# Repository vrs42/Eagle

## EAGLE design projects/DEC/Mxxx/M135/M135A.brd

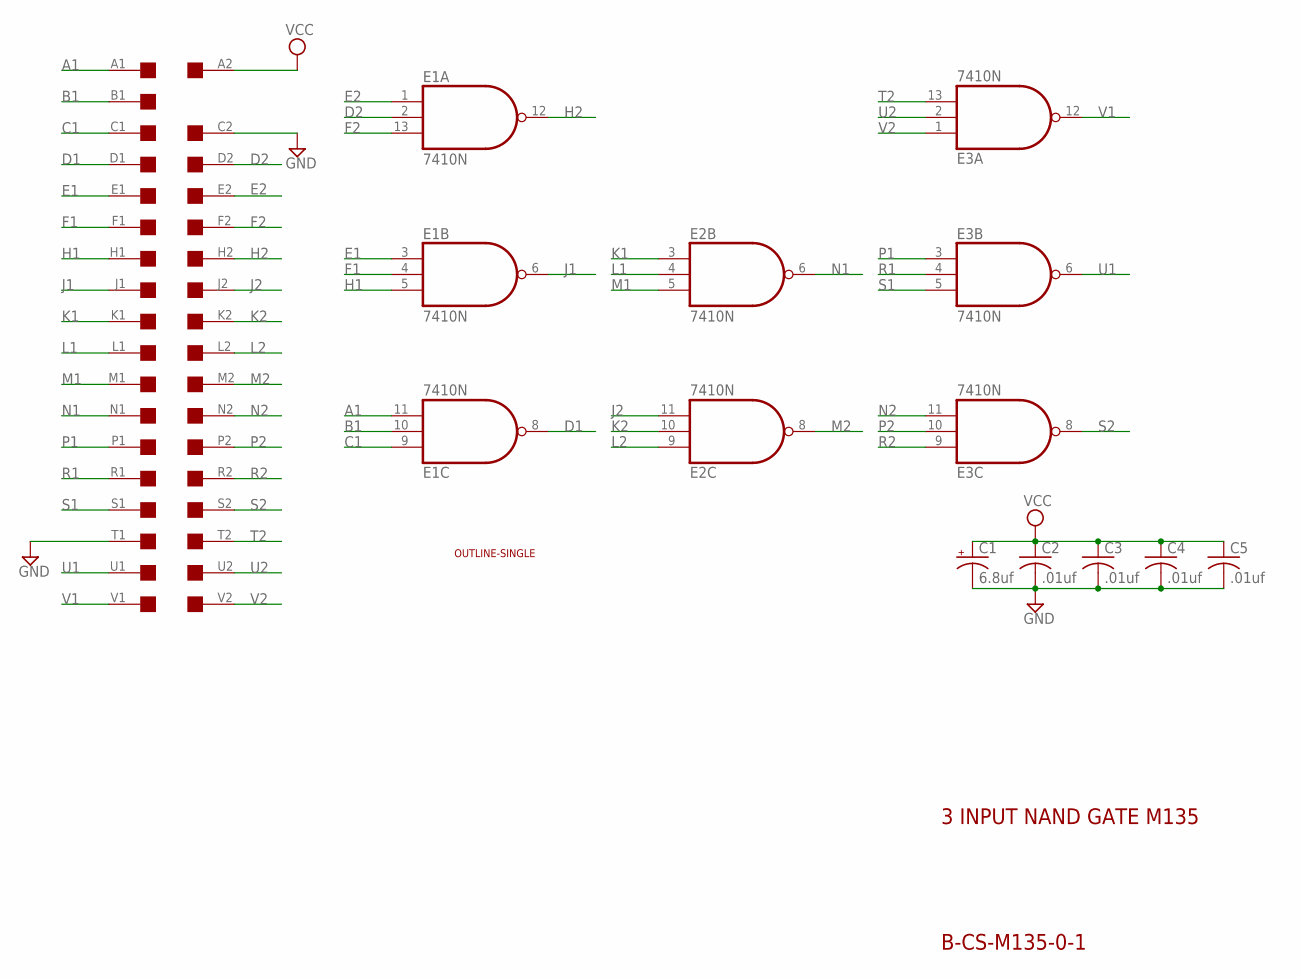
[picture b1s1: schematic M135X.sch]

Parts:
C1: 6.8uf; E15-5
C2, C3, C4, C5: .01uf; C050-025X075
E1, E2, E3: 7410N; DIL14
U$1: SINGLE; EDGE-CON2
U$4: OUTLINE-SINGLE; SINGLE

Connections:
A1: E1.11 (I2), U$1.A1
B1: E1.10 (I1), U$1.B1
C1: E1.9 (I0), U$1.C1
D1: E1.8 (O), U$1.D1
D2: E1.2 (I1), U$1.D2
E1: E1.3 (I0), U$1.E1
E2: E1.1 (I0), U$1.E2
F1: E1.4 (I1), U$1.F1
F2: E1.13 (I2), U$1.F2
GND: C1.-, C2.2, C3.2, C4.2, C5.2, E1.7 (GND), E2.7 (GND), E3.7 (GND), U$1.C2, U$1.T1
H1: E1.5 (I2), U$1.H1
H2: E1.12 (O), U$1.H2
J1: E1.6 (O), U$1.J1
J2: E2.11 (I2), U$1.J2
K1: E2.3 (I0), U$1.K1
K2: E2.10 (I1), U$1.K2
L1: E2.4 (I1), U$1.L1
L2: E2.9 (I0), U$1.L2
M1: E2.5 (I2), U$1.M1
M2: E2.8 (O), U$1.M2
N1: E2.6 (O), U$1.N1
N2: E3.11 (I2), U$1.N2
P1: E3.3 (I0), U$1.P1
P2: E3.10 (I1), U$1.P2
R1: E3.4 (I1), U$1.R1
R2: E3.9 (I0), U$1.R2
S1: E3.5 (I2), U$1.S1
S2: E3.8 (O), U$1.S2
T2: E3.13 (I2), U$1.T2
U1: E3.6 (O), U$1.U1
U2: E3.2 (I1), U$1.U2
V1: E3.12 (O), U$1.V1
V2: E3.1 (I0), U$1.V2
VCC: C1.+, C2.1, C3.1, C4.1, C5.1, E1.14 (VCC), E2.14 (VCC), E3.14 (VCC), U$1.A2

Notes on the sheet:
3 INPUT NAND GATE M135
B-CS-M135-0-1

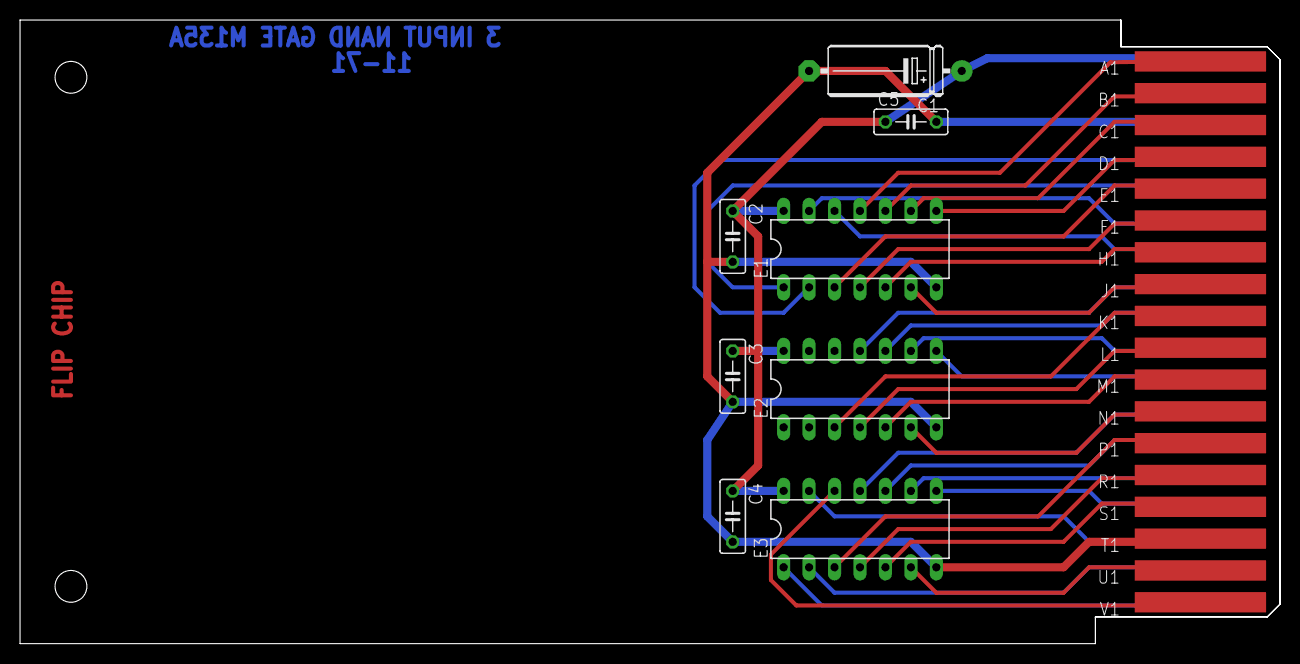
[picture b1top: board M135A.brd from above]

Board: 2 copper layers, 125.7 x 62.2 mm, 10 parts (0 on the bottom side), 34 nets.

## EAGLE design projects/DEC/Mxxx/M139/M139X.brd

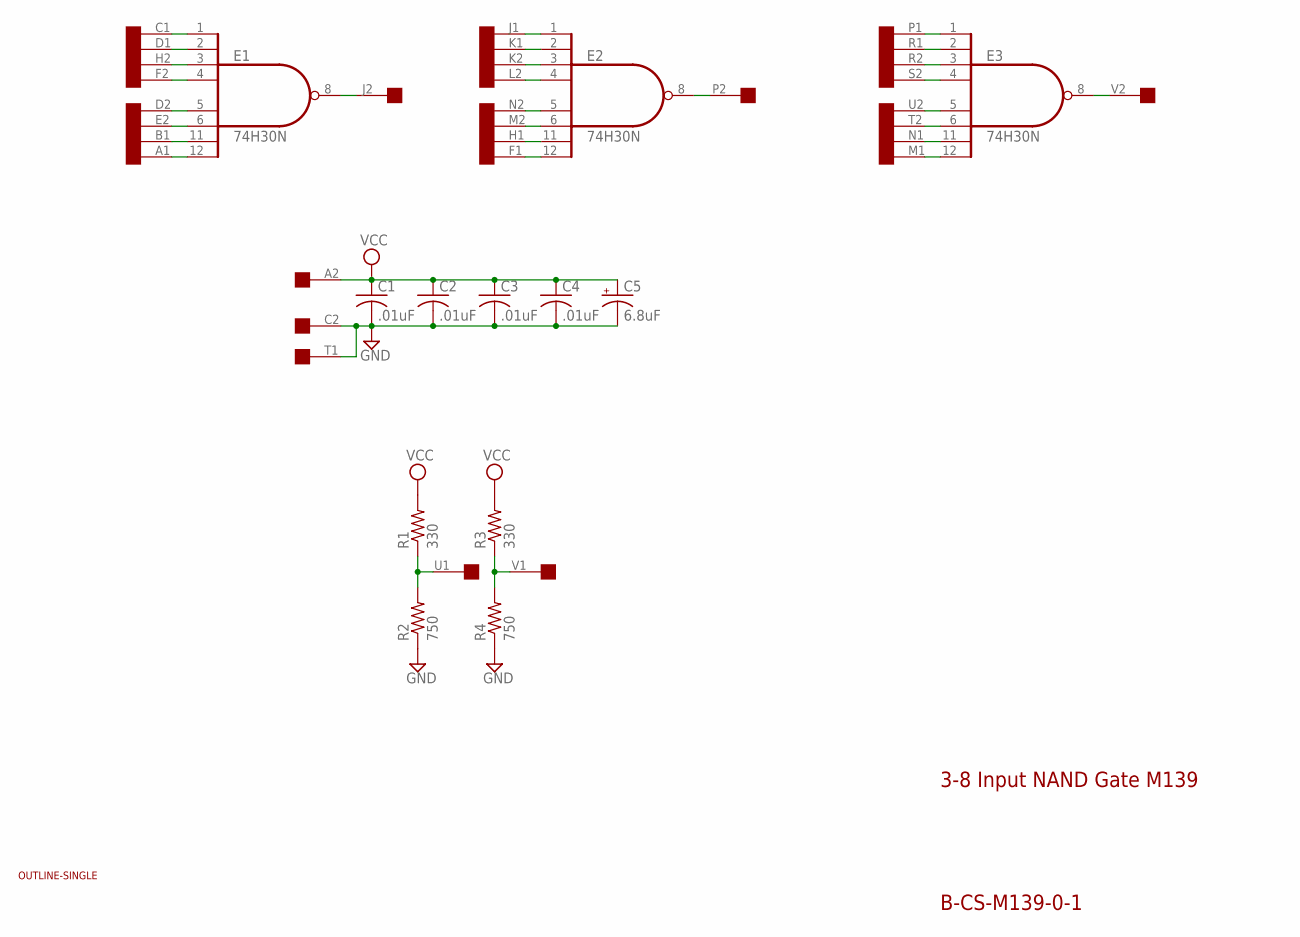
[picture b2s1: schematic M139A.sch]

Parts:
C1, C2, C3, C4: .01uF; C050-025X075
C5: 6.8uF; E12-8
E1, E2, E3: 74H30N; DIL14
R1, R3: 330; 0207/10
R2, R4: 750; 0207/10
U$1: OUTLINE-SINGLE; SINGLE
U$2: SINGLE; EDGE-CON2

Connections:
GND: C1.2, C2.2, C3.2, C4.2, C5.-, E1.7 (GND), E2.7 (GND), E3.7 (GND), R2.1, R4.1, U$2.C2, U$2.T1
unnamed: E1.1 (I0), U$2.C1
unnamed: E1.2 (I1), U$2.D1
unnamed: E1.3 (I2), U$2.H2
unnamed: E1.4 (I3), U$2.F2
unnamed: E1.6 (I5), U$2.E2
unnamed: E1.5 (I4), U$2.D2
unnamed: E1.11 (I6), U$2.B1
unnamed: E1.12 (I7), U$2.A1
unnamed: E1.8 (O), U$2.J2
unnamed: E2.1 (I0), U$2.J1
unnamed: E2.2 (I1), U$2.K1
unnamed: E2.3 (I2), U$2.K2
unnamed: E2.4 (I3), U$2.L2
unnamed: E2.5 (I4), U$2.N2
unnamed: E2.6 (I5), U$2.M2
unnamed: E2.8 (O), U$2.P2
unnamed: E2.11 (I6), U$2.H1
unnamed: E2.12 (I7), U$2.F1
unnamed: E3.8 (O), U$2.V2
unnamed: E3.1 (I0), U$2.P1
unnamed: E3.2 (I1), U$2.R1
unnamed: E3.3 (I2), U$2.R2
unnamed: E3.4 (I3), U$2.S2
unnamed: E3.5 (I4), U$2.U2
unnamed: E3.6 (I5), U$2.T2
unnamed: E3.12 (I7), U$2.M1
unnamed: E3.11 (I6), U$2.N1
unnamed: R1.1, R2.2, U$2.U1
unnamed: R3.1, R4.2, U$2.V1
VCC: C1.1, C2.1, C3.1, C4.1, C5.+, E1.14 (VCC), E2.14 (VCC), E3.14 (VCC), R1.2, R3.2, U$2.A2

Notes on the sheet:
3-8 Input NAND Gate M139
B-CS-M139-0-1

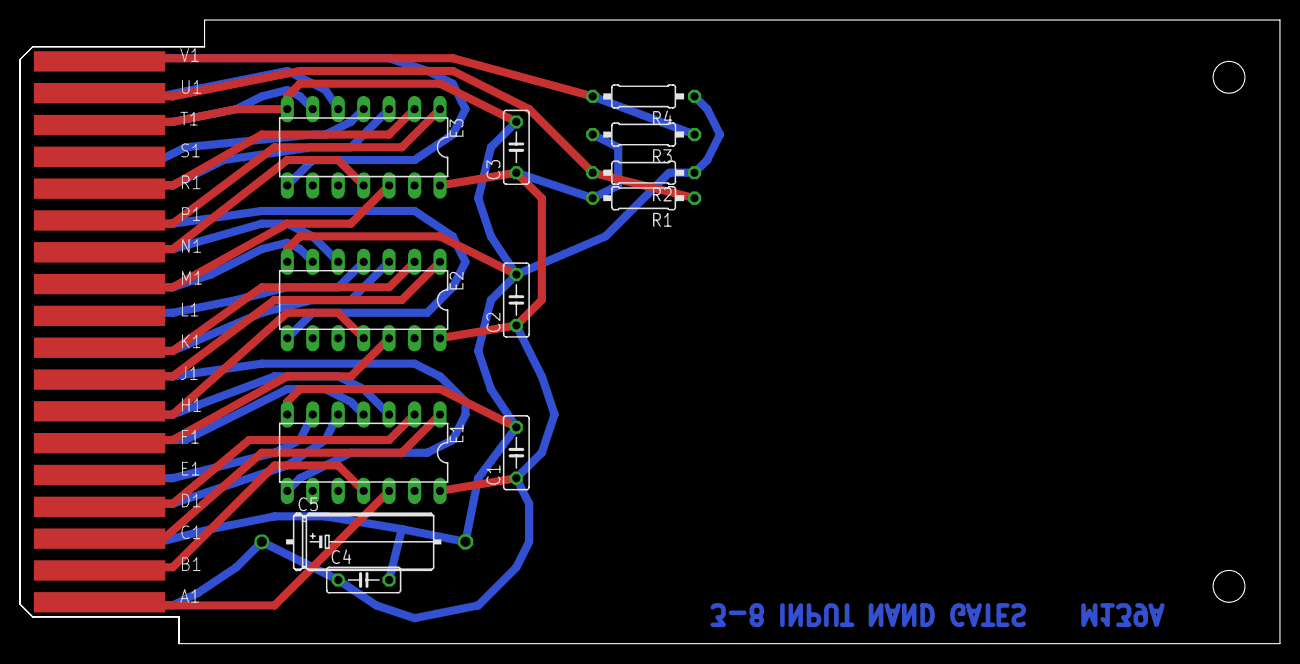
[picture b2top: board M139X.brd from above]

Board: 2 copper layers, 125.7 x 62.2 mm, 14 parts (0 on the bottom side), 31 nets.

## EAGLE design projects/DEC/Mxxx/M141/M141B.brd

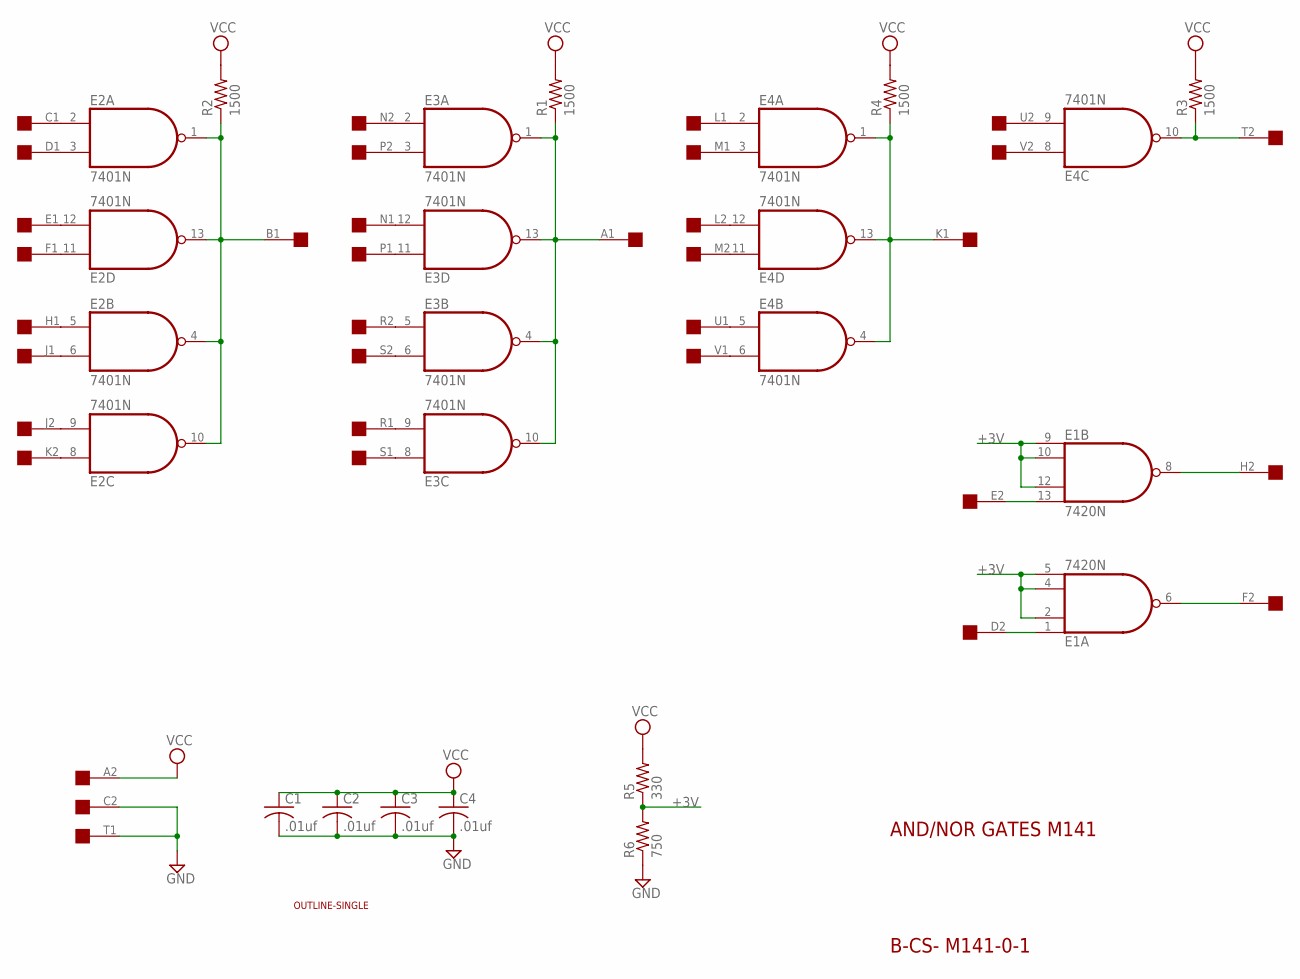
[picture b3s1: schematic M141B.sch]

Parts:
C1, C2, C3, C4: .01uf; C050-025X075
E1: 7420N; DIL14
E2, E3, E4: 7401N; DIL14
R1, R2, R3, R4: 1500; 0207/10
R5: 330; 0207/10
R6: 750; 0207/10
U$1: OUTLINE-SINGLE; SINGLE
U$4: SINGLE; EDGE-CON2

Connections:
+3V: E1.2 (I1), E1.4 (I2), E1.5 (I3), E1.9 (I0), E1.10 (I1), E1.12 (I2), R5.1, R6.2
GND: C1.2, C2.2, C3.2, C4.2, E1.7 (GND), E2.7 (GND), E3.7 (GND), E4.7 (GND), R6.1, U$4.C2, U$4.T1
unnamed: E2.2 (I0), U$4.C1
unnamed: E2.3 (I1), U$4.D1
unnamed: E2.12 (I1), U$4.E1
unnamed: E2.11 (I0), U$4.F1
unnamed: E2.5 (I0), U$4.H1
unnamed: E2.6 (I1), U$4.J1
unnamed: E2.8 (I0), U$4.K2
unnamed: E2.9 (I1), U$4.J2
unnamed: E2.1 (O), E2.4 (O), E2.10 (O), E2.13 (O), R2.1, U$4.B1
unnamed: E3.3 (I1), U$4.P2
unnamed: E3.2 (I0), U$4.N2
unnamed: E3.12 (I1), U$4.N1
unnamed: E3.11 (I0), U$4.P1
unnamed: E3.6 (I1), U$4.S2
unnamed: E3.5 (I0), U$4.R2
unnamed: E3.9 (I1), U$4.R1
unnamed: E3.8 (I0), U$4.S1
unnamed: E3.1 (O), E3.4 (O), E3.10 (O), E3.13 (O), R1.1, U$4.A1
unnamed: E4.12 (I1), U$4.L2
unnamed: E4.11 (I0), U$4.M2
unnamed: E4.2 (I0), U$4.L1
unnamed: E4.3 (I1), U$4.M1
unnamed: E4.5 (I0), U$4.U1
unnamed: E4.6 (I1), U$4.V1
unnamed: E4.1 (O), E4.4 (O), E4.13 (O), R4.1, U$4.K1
unnamed: E4.9 (I1), U$4.U2
unnamed: E4.8 (I0), U$4.V2
unnamed: E4.10 (O), R3.1, U$4.T2
unnamed: E1.8 (O), U$4.H2
unnamed: E1.6 (O), U$4.F2
unnamed: E1.13 (I3), U$4.E2
unnamed: E1.1 (I0), U$4.D2
VCC: C1.1, C2.1, C3.1, C4.1, E1.14 (VCC), E2.14 (VCC), E3.14 (VCC), E4.14 (VCC), R1.2, R2.2, R3.2, R4.2, R5.2, U$4.A2

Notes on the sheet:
AND/NOR GATES M141
B-CS- M141-0-1

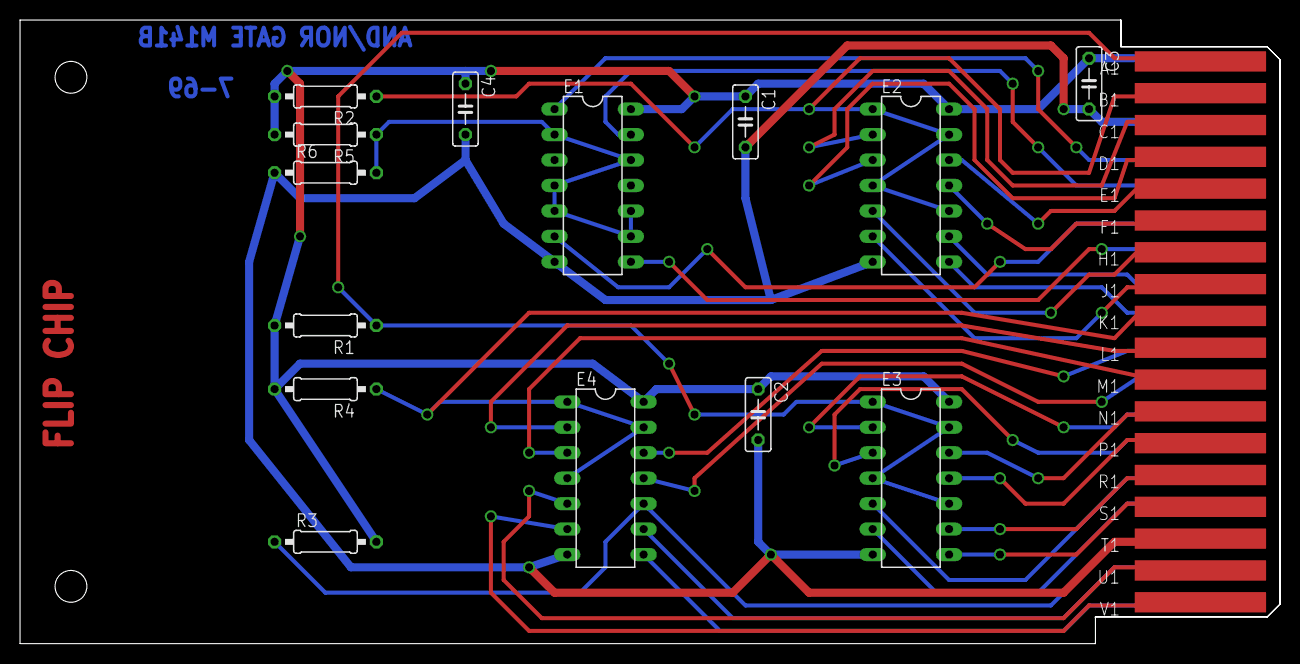
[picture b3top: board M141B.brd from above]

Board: 2 copper layers, 125.7 x 62.2 mm, 17 parts (0 on the bottom side), 35 nets.

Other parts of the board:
U$2: FLIPCHIP

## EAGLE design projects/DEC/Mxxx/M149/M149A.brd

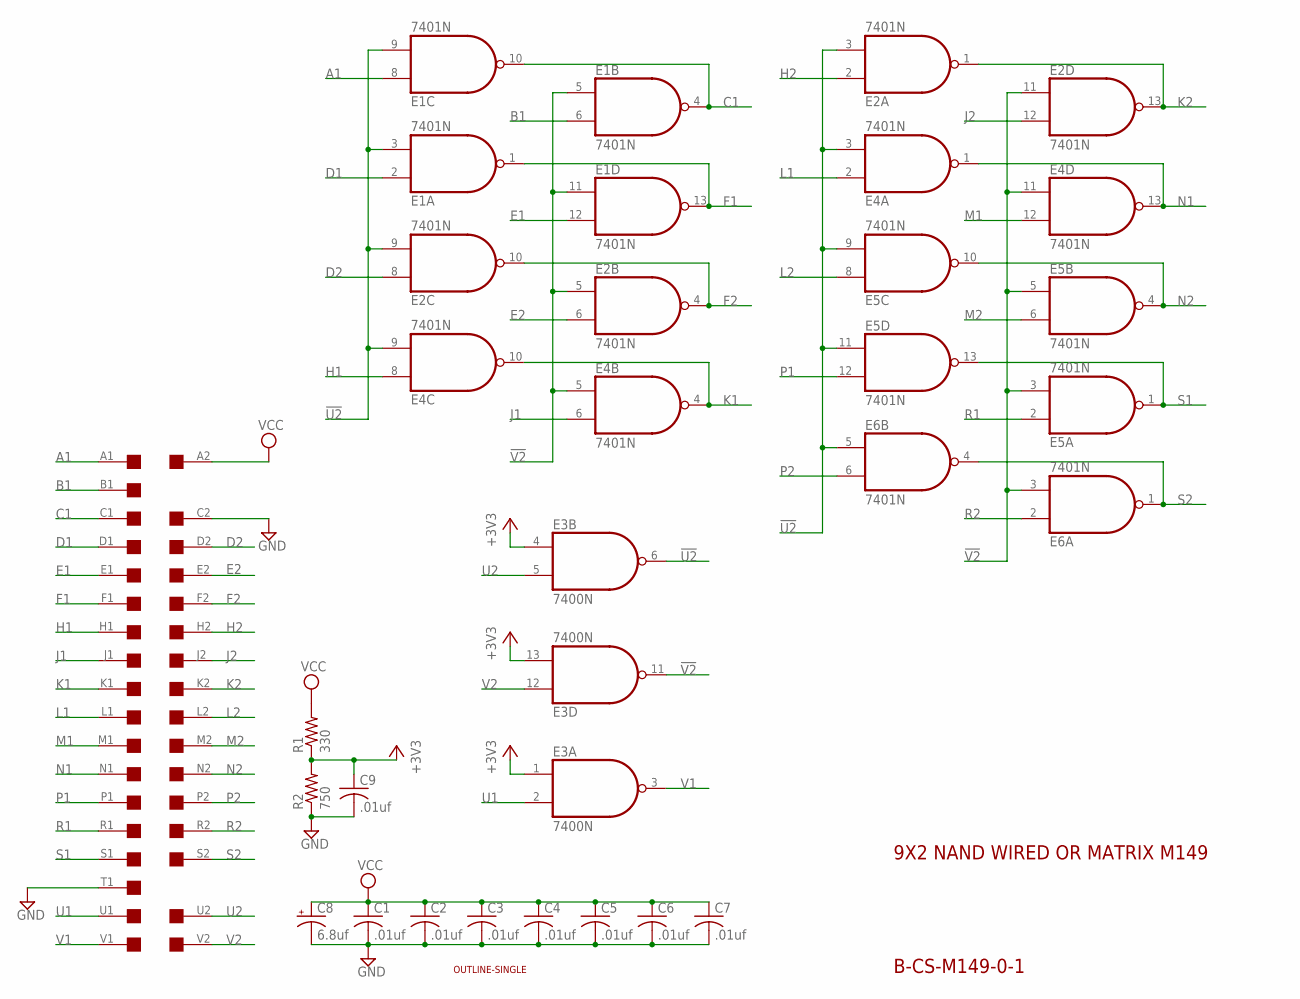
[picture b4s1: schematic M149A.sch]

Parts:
C1, C2, C3, C4, C5, C6, C7, C9: .01uf; C050-025X075
C8: 6.8uf; E15-5
E1, E2, E4, E5, E6: 7401N; DIL14
E3: 7400N; DIL14
R1: 330; 0207/10
R2: 750; 0207/10
U$1: SINGLE; EDGE-CON2
U$4: OUTLINE-SINGLE; SINGLE

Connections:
!U2: E1.3 (I1), E1.9 (I1), E2.3 (I1), E2.9 (I1), E3.6 (O), E4.3 (I1), E4.9 (I1), E5.9 (I1), E5.11 (I0), E6.5 (I0)
!V2: E1.5 (I0), E1.11 (I0), E2.5 (I0), E2.11 (I0), E3.11 (O), E4.5 (I0), E4.11 (I0), E5.3 (I1), E5.5 (I0), E6.3 (I1)
+3V3: C9.1, E3.1 (I0), E3.4 (I0), E3.13 (I1), R1.1, R2.2
A1: E1.8 (I0), U$1.A1
B1: E1.6 (I1), U$1.B1
C1: E1.4 (O), E1.10 (O), U$1.C1
D1: E1.2 (I0), U$1.D1
D2: E2.8 (I0), U$1.D2
E1: E1.12 (I1), U$1.E1
E2: E2.6 (I1), U$1.E2
F1: E1.1 (O), E1.13 (O), U$1.F1
F2: E2.4 (O), E2.10 (O), U$1.F2
GND: C1.2, C2.2, C3.2, C4.2, C5.2, C6.2, C7.2, C8.-, C9.2, E1.7 (GND), E2.7 (GND), E3.7 (GND), E4.7 (GND), E5.7 (GND), E6.7 (GND), R2.1, U$1.C2, U$1.T1
H1: E4.8 (I0), U$1.H1
H2: E2.2 (I0), U$1.H2
J1: E4.6 (I1), U$1.J1
J2: E2.12 (I1), U$1.J2
K1: E4.4 (O), E4.10 (O), U$1.K1
K2: E2.1 (O), E2.13 (O), U$1.K2
L1: E4.2 (I0), U$1.L1
L2: E5.8 (I0), U$1.L2
M1: E4.12 (I1), U$1.M1
M2: E5.6 (I1), U$1.M2
N1: E4.1 (O), E4.13 (O), U$1.N1
N2: E5.4 (O), E5.10 (O), U$1.N2
P1: E5.12 (I1), U$1.P1
P2: E6.6 (I1), U$1.P2
R1: E5.2 (I0), U$1.R1
R2: E6.2 (I0), U$1.R2
S1: E5.1 (O), E5.13 (O), U$1.S1
S2: E6.1 (O), E6.4 (O), U$1.S2
U1: E3.2 (I1), U$1.U1
U2: E3.5 (I1), U$1.U2
V1: E3.3 (O), U$1.V1
V2: E3.12 (I0), U$1.V2
VCC: C1.1, C2.1, C3.1, C4.1, C5.1, C6.1, C7.1, C8.+, E1.14 (VCC), E2.14 (VCC), E3.14 (VCC), E4.14 (VCC), E5.14 (VCC), E6.14 (VCC), R1.2, U$1.A2

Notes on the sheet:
9X2 NAND WIRED OR MATRIX M149
B-CS-M149-0-1

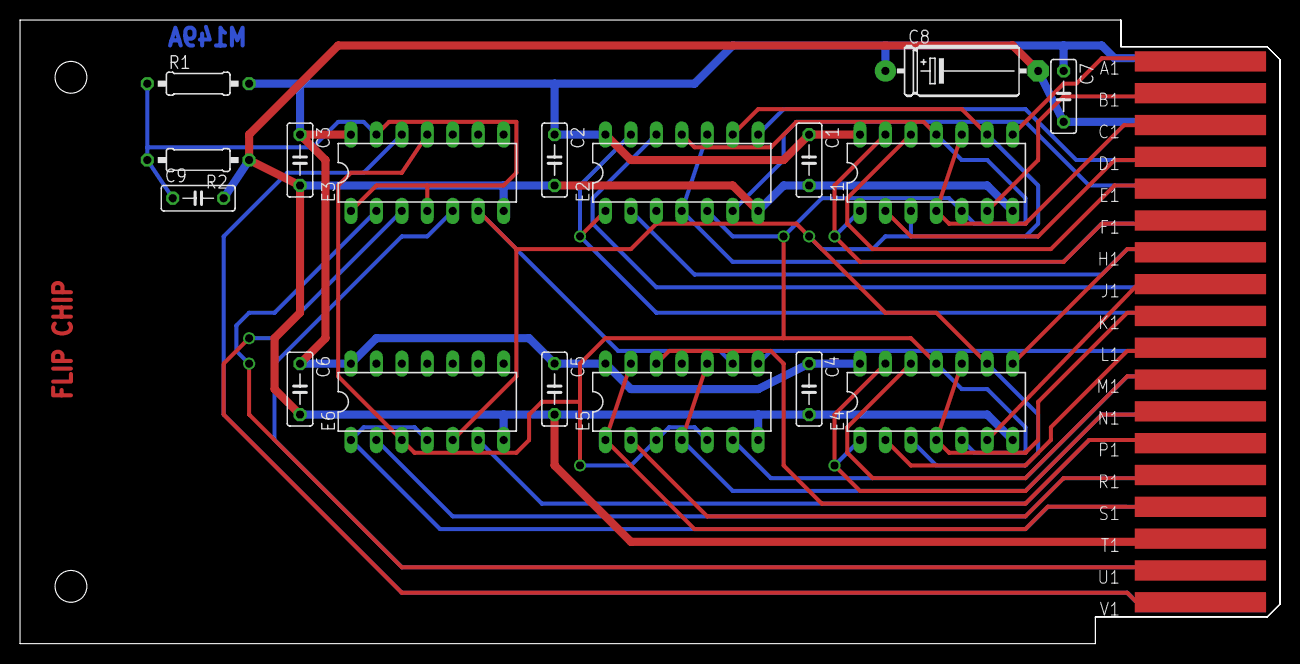
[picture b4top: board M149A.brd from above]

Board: 2 copper layers, 125.7 x 62.2 mm, 19 parts (0 on the bottom side), 36 nets.
